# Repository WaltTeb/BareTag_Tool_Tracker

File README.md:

# Baretag Tool-Tracker

Item locating and theft prevention system built around the DWM3001C using Ultra Wideband, BLE, and LoRa technologies.

## Hardware

Qorvo DWM3001C - UWB & BLE SoC using nRF52833 and Qorvo DWM3000  

Reyax RYLR998 - LoRa  

3.7V 290mAh LiPo - Tag Battery  

3.7 2200mAh LiIon - Anchor Battery  

CP2102 Serial Converter - LoRa to Serial  

Raspberry Pi 4B - Host for Lora processing  

Dell NUC - Host for servers  

Tag-Connect Edge-Connect Programmer - Programming Tag PCBs  

SEGGER JLink Edu Mini - Programming Anchor PCBs  

## Software

SEGGER Embedded Studio - Build environement  

nRF5 SDK - Nordic libraries for nRF52833  

Xcode - UI/UX  

Debian Linux - Light distro for NUC  

J-Flash Lite - Flashing firmware to DWM3001C  

SQLite - Database management  

Electron - App development  

KiCad - PCB design   
 
# Setup

Run the shell script that we have yet to make in order to install project dependencies
This will create a working project development environment

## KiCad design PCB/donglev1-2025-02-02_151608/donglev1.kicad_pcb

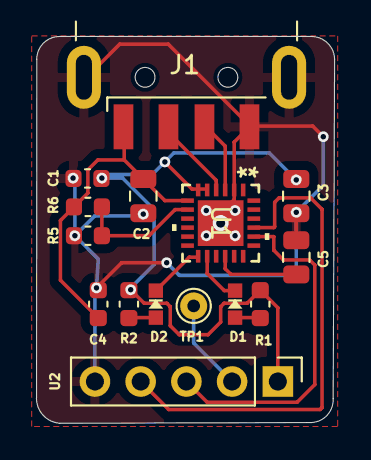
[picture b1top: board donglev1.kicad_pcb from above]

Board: 2 copper layers, 16.6 x 21.5 mm, 15 parts (0 on the bottom side), 12 nets.

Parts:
C1, C4: C0603C104J4RACTU; C_0603_1608Metric
C2, C3, C5: C0603C106M9PAC7867; C_0805_2012Metric
D1: D1; CHIPLED_0603_NOOUTLINE
D2: D2; CHIPLED_0603_NOOUTLINE
J1: 1734028-1; USB_A_CNCTech_1001-011-01101_Horizontal
R1, R2, R6: RT0603BRD0720KL; C_0603_1608Metric
R5: RC0603FR-0747KL; C_0603_1608Metric
TP1: TestPoint; TestPoint_THTPad_D1.5mm_Drill0.7mm
U1: CP2102N-24; QFN24_CP2102N_SIL-L
U2: RYLR998; PinHeader_1x05_P2.54mm_Vertical

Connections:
+3.3V: C1.1, C3.1, R1.2, R2.2, U1.5 (VIO), U1.6 (VDD), U2.1
+5V: C2.1, C4.1, J1.1 (VBUS), R6.2, U1.7 (REGIN)
/D+: J1.3 (D+), U1.3 (D+)
/D-: J1.2 (D-), U1.4 (D-)
/RSTL: TP1.1, U2.2
/RX: U1.20 (RXD), U2.3
/TX: U1.21 (TXD), U2.4
/VBUS_DETECT: R5.2, R6.1, U1.8 (VBUS)
GND: C1.2, C2.2, C3.2, C4.2, C5.2, J1.4 (GND), J1.5 (Shield), R5.1, U1.2 (GND), U2.5
unnamed: C5.1, U1.16 (CP2014VREG)
unnamed: D1.C, U1.14 (GPIO0/TXLED)
unnamed: D2.C, U1.13 (GPIO1/RXLED)

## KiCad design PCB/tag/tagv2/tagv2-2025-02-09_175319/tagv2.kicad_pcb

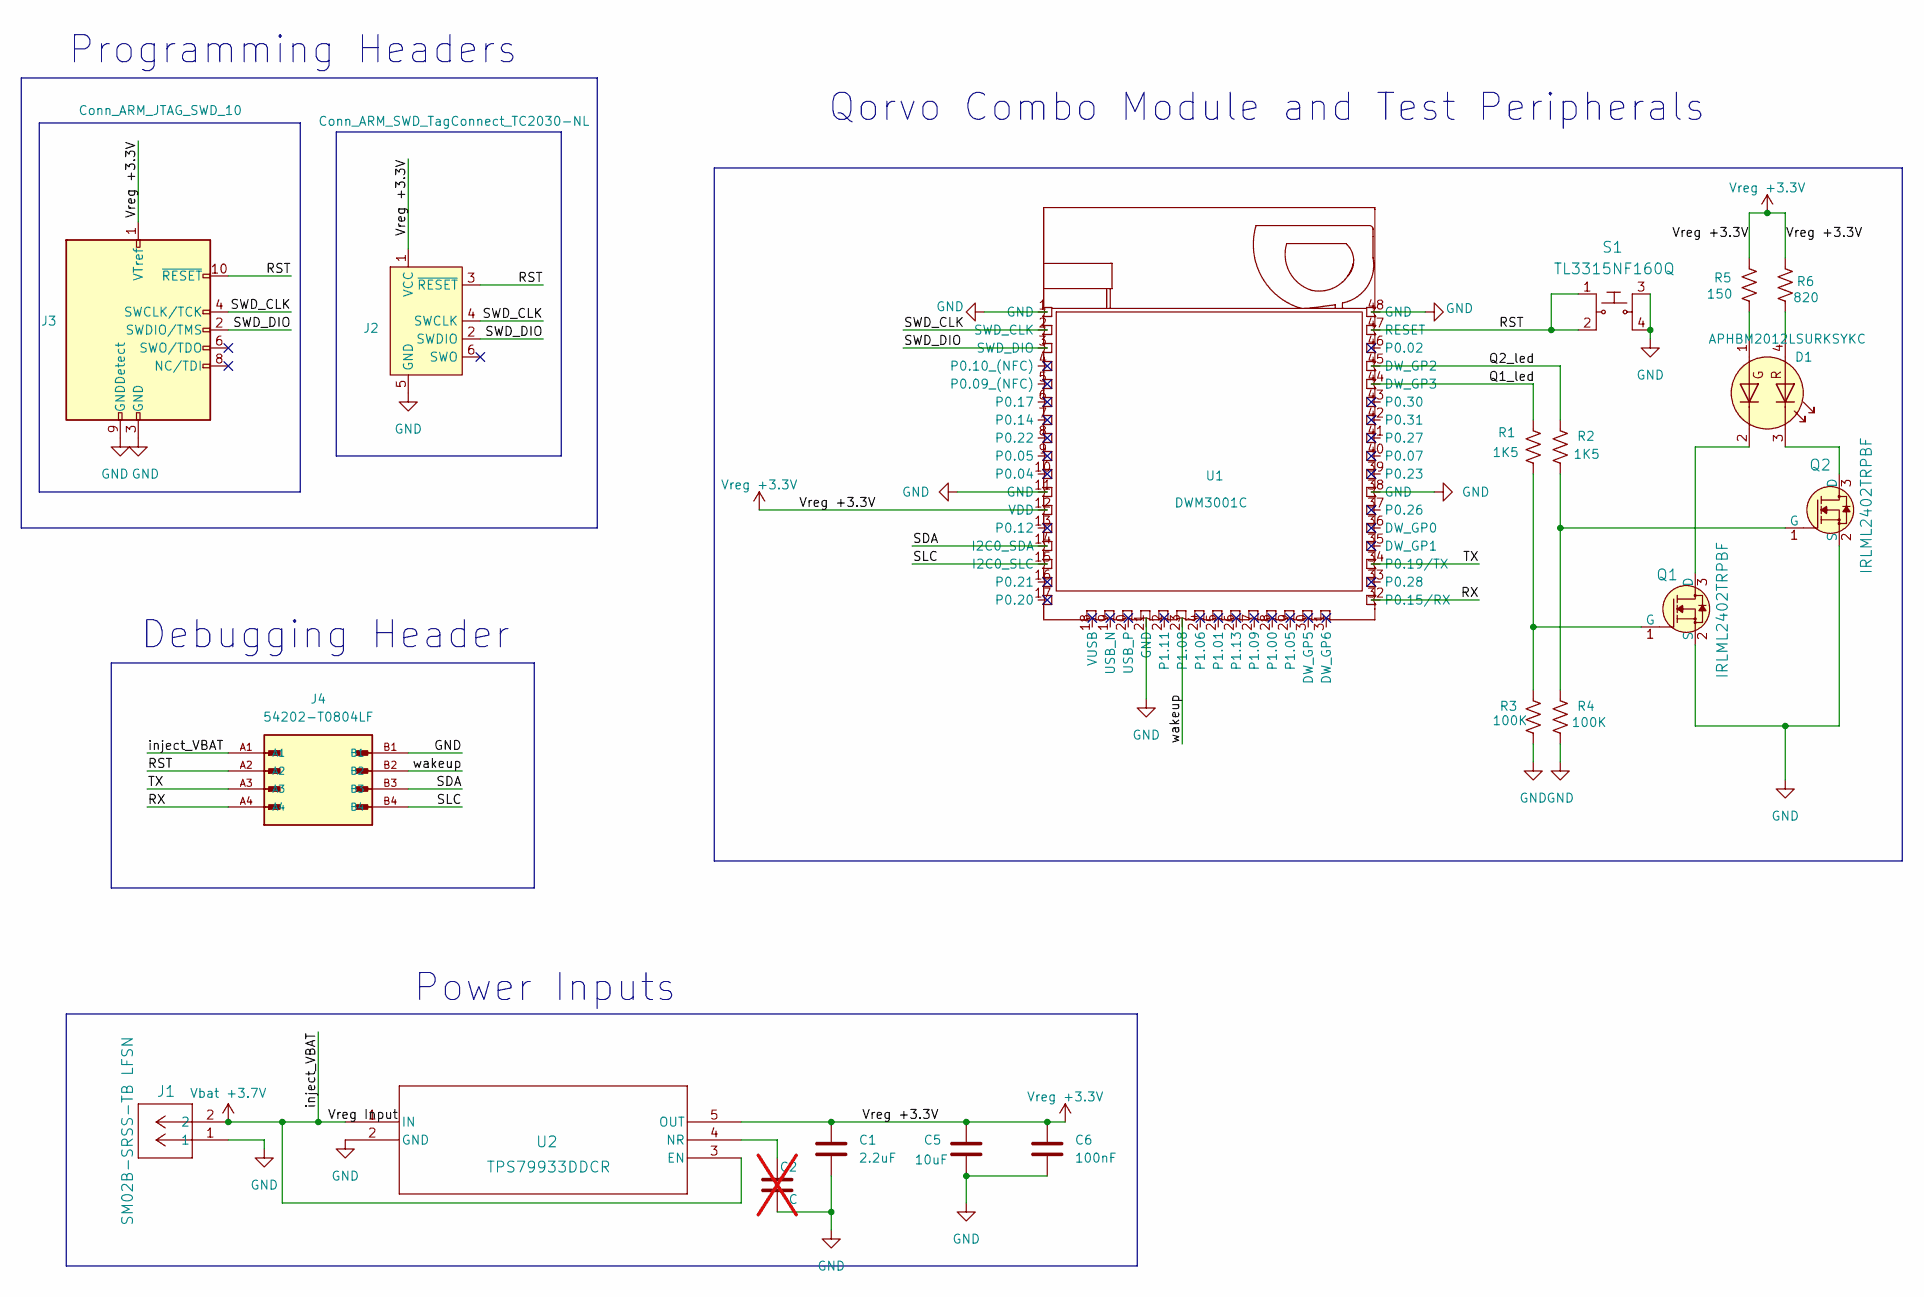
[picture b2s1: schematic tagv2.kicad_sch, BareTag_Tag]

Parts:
C1: 2.2uF; GRM155C80J225KE95D
C2: C; GRM155C80J225KE95D; not fitted
C5: 10uF; GRM155C80J225KE95D
C6: 100nF; C_0603_1608Metric
D1: APHBM2012LSURKSYKC; LED_APHBM2012LSURKSYKC
J1: SM02B-SRSS-TB LFSN; SM02BSRSSTBLFSN
J2: Conn_ARM_SWD_TagConnect_TC2030-NL
J3: Conn_ARM_JTAG_SWD_10; PinHeader_2x05_P1.27mm_Vertical_SMD
J4: 54202-T0804LF; AMPHENOL_54202-T0804LF; PARTREV AC
Q1, Q2: IRLML2402TRPBF; SOT-23-3; MPN IRLML2402TRPBF; Digi-Key_PN IRLML2402PBFCT-ND
R1, R2: 1K5; R_0402_1005Metric
R3, R4: 100K; R_0402_1005Metric
R5: 150; R_0402_1005Metric
R6: 820; R_0402_1005Metric
S1: TL3315NF160Q; Switch_Tactile_SMD_4.5x4.5mm_TL3315NF160Q; MPN TL3315NF160Q; Digi-Key_PN EG4621CT-ND
U1: DWM3001C
U2: TPS79933DDCR; SOT95P280X110-5N

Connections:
/Q1_led: R1.1, U1.44 (DW_GP3)
/Q2_led: R2.1, U1.45 (DW_GP2)
/RST: J2.3 (~RESET), J3.10 (~RESET), J4.A2, S1.1, S1.2, U1.47 (RESET); also elsewhere on the board
/RX: J4.A4, U1.32 (P0.15/RX); also elsewhere on the board
/SDA: J4.B3, U1.14 (I2C0_SDA); also elsewhere on the board
/SLC: J4.B4, U1.15 (I2C0_SLC); also elsewhere on the board
/SWD_CLK: J2.4 (SWCLK), J3.4 (SWCLK/TCK), U1.2 (SWD_CLK)
/SWD_DIO: J2.2 (SWDIO), J3.2 (SWDIO/TMS), U1.3 (SWD_DIO)
/TX: J4.A3, U1.34 (P0.19/TX); also elsewhere on the board
/wakeup: J4.B2, U1.23 (P1.08); also elsewhere on the board
GND: C1.1, C2.2, C5.2, C6.2, J1.1, J2.5 (GND), J3.3 (GND), J3.5 (GND), J3.9 (GNDDetect), Q1.2 (S), Q2.2 (S), R3.2, R4.2, S1.3, S1.4, U1.1 (GND), U1.11 (GND), U1.21 (GND), U1.38 (GND), U1.48 (GND), U2.2 (GND); also elsewhere on the board
unnamed: D1.4 (A1), R6.2
unnamed: D1.1 (A2), R5.2
unnamed: D1.3 (K1), Q2.3 (D)
unnamed: D1.2 (K2), Q1.3 (D)
unnamed: Q1.1 (G), R1.2, R3.1
unnamed: Q2.1 (G), R2.2, R4.1
unnamed: C2.1, U2.4 (NR)
Vbat +3.7V: J1.2, J4.A1, U2.1 (IN), U2.3 (EN); also elsewhere on the board
Vreg +3.3V: C1.2, C5.1, C6.1, J2.1 (VCC), J3.1 (VTref), R5.1, R6.1, U1.12 (VDD), U2.5 (OUT)

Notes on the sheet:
Qorvo Combo Module and Test Peripherals
Debugging Header
Power Inputs
Programming Headers

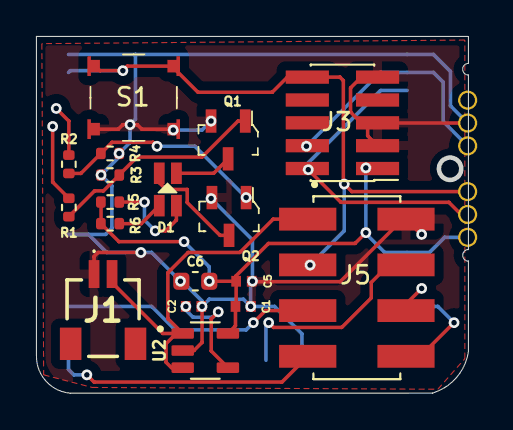
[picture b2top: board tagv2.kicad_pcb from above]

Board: 2 copper layers, 23.8 x 19.6 mm, 19 parts (1 on the bottom side), 20 nets.

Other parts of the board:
J5: 54202-T0804LF; AMPHENOL_54202-T0804LF

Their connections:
/RST: J5.A2; also elsewhere on the board
/RX: J5.A4; also elsewhere on the board
/SDA: J5.B3; also elsewhere on the board
/SLC: J5.B4; also elsewhere on the board
/TX: J5.A3; also elsewhere on the board
/wakeup: J5.B2; also elsewhere on the board
GND: J5.B1; also elsewhere on the board
Vbat +3.7V: J5.A1; also elsewhere on the board

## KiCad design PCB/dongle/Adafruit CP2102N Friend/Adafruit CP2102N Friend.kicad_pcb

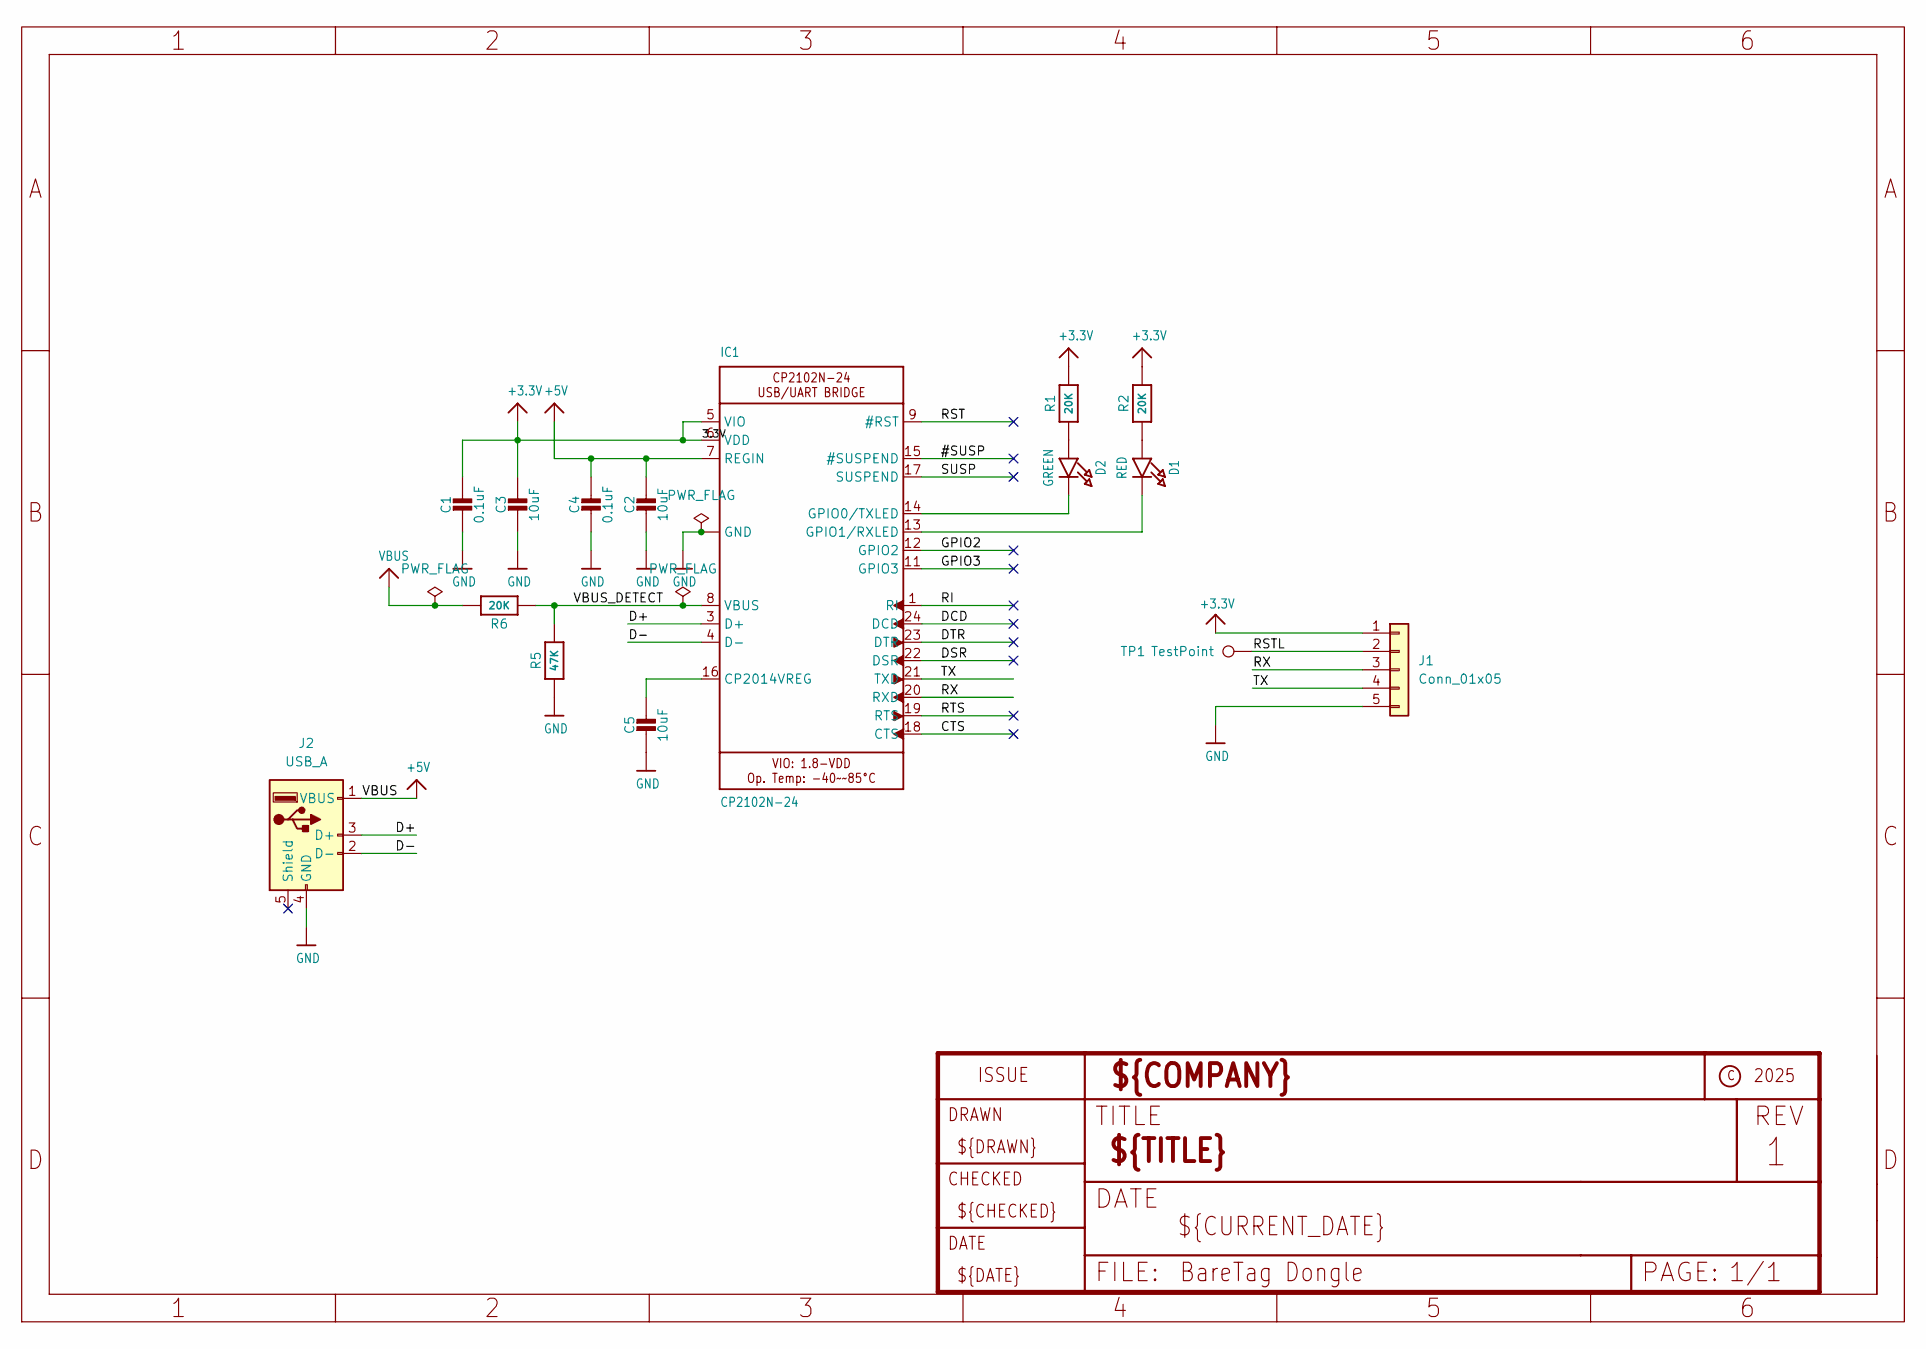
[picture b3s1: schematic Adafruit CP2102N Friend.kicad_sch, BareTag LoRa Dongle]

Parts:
C1, C4: 0.1uF; C_0603_1608Metric
C2, C3, C5: 10uF; C_0805_2012Metric
D1: RED; CHIPLED_0603_NOOUTLINE
D2: GREEN; CHIPLED_0603_NOOUTLINE
IC1: CP2102N-24; QFN24_CP2102N_SIL
J1: Conn_01x05; PinHeader_1x05_P2.54mm_Vertical
J2: USB_A; 17340281
R1, R2, R6: 20K; C_0603_1608Metric
R5: 47K; C_0603_1608Metric
TP1: TestPoint; TestPoint_THTPad_D1.5mm_Drill0.7mm

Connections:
+3.3V: C1.1, C3.1, IC1.5 (VIO), IC1.6 (VDD), J1.1, R1.2, R2.2
+5V: C2.1, C4.1, IC1.7 (REGIN), J2.1 (VBUS), R6.2
/#SUSP: IC1.15 (#SUSPEND)
/CTS: IC1.18 (CTS)
/D+: IC1.3 (D+), J2.3 (D+)
/D-: IC1.4 (D-), J2.2 (D-)
/DCD: IC1.24 (DCD)
/DSR: IC1.22 (DSR)
/DTR: IC1.23 (DTR)
/GPIO2: IC1.12 (GPIO2)
/GPIO3: IC1.11 (GPIO3)
/RI: IC1.1 (RI)
/RST: IC1.9 (#RST)
/RSTL: J1.2, TP1.1
/RTS: IC1.19 (RTS)
/RX: IC1.20 (RXD), J1.3
/SUSP: IC1.17 (SUSPEND)
/TX: IC1.21 (TXD), J1.4
/VBUS_DETECT: IC1.8 (VBUS), R5.2, R6.1
GND: C1.2, C2.2, C3.2, C4.2, C5.2, IC1.2 (GND), IC1.THERM (GND), J1.5, J2.4 (GND), R5.1
unnamed: D1.A, R2.1
unnamed: D2.A, R1.1
unnamed: C5.1, IC1.16 (CP2014VREG)
unnamed: D2.C, IC1.14 (GPIO0/TXLED)
unnamed: D1.C, IC1.13 (GPIO1/RXLED)

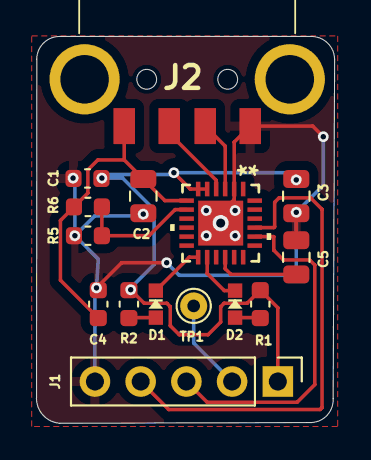
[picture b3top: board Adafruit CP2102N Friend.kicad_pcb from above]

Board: 2 copper layers, 16.6 x 21.5 mm, 15 parts (0 on the bottom side), 14 nets.

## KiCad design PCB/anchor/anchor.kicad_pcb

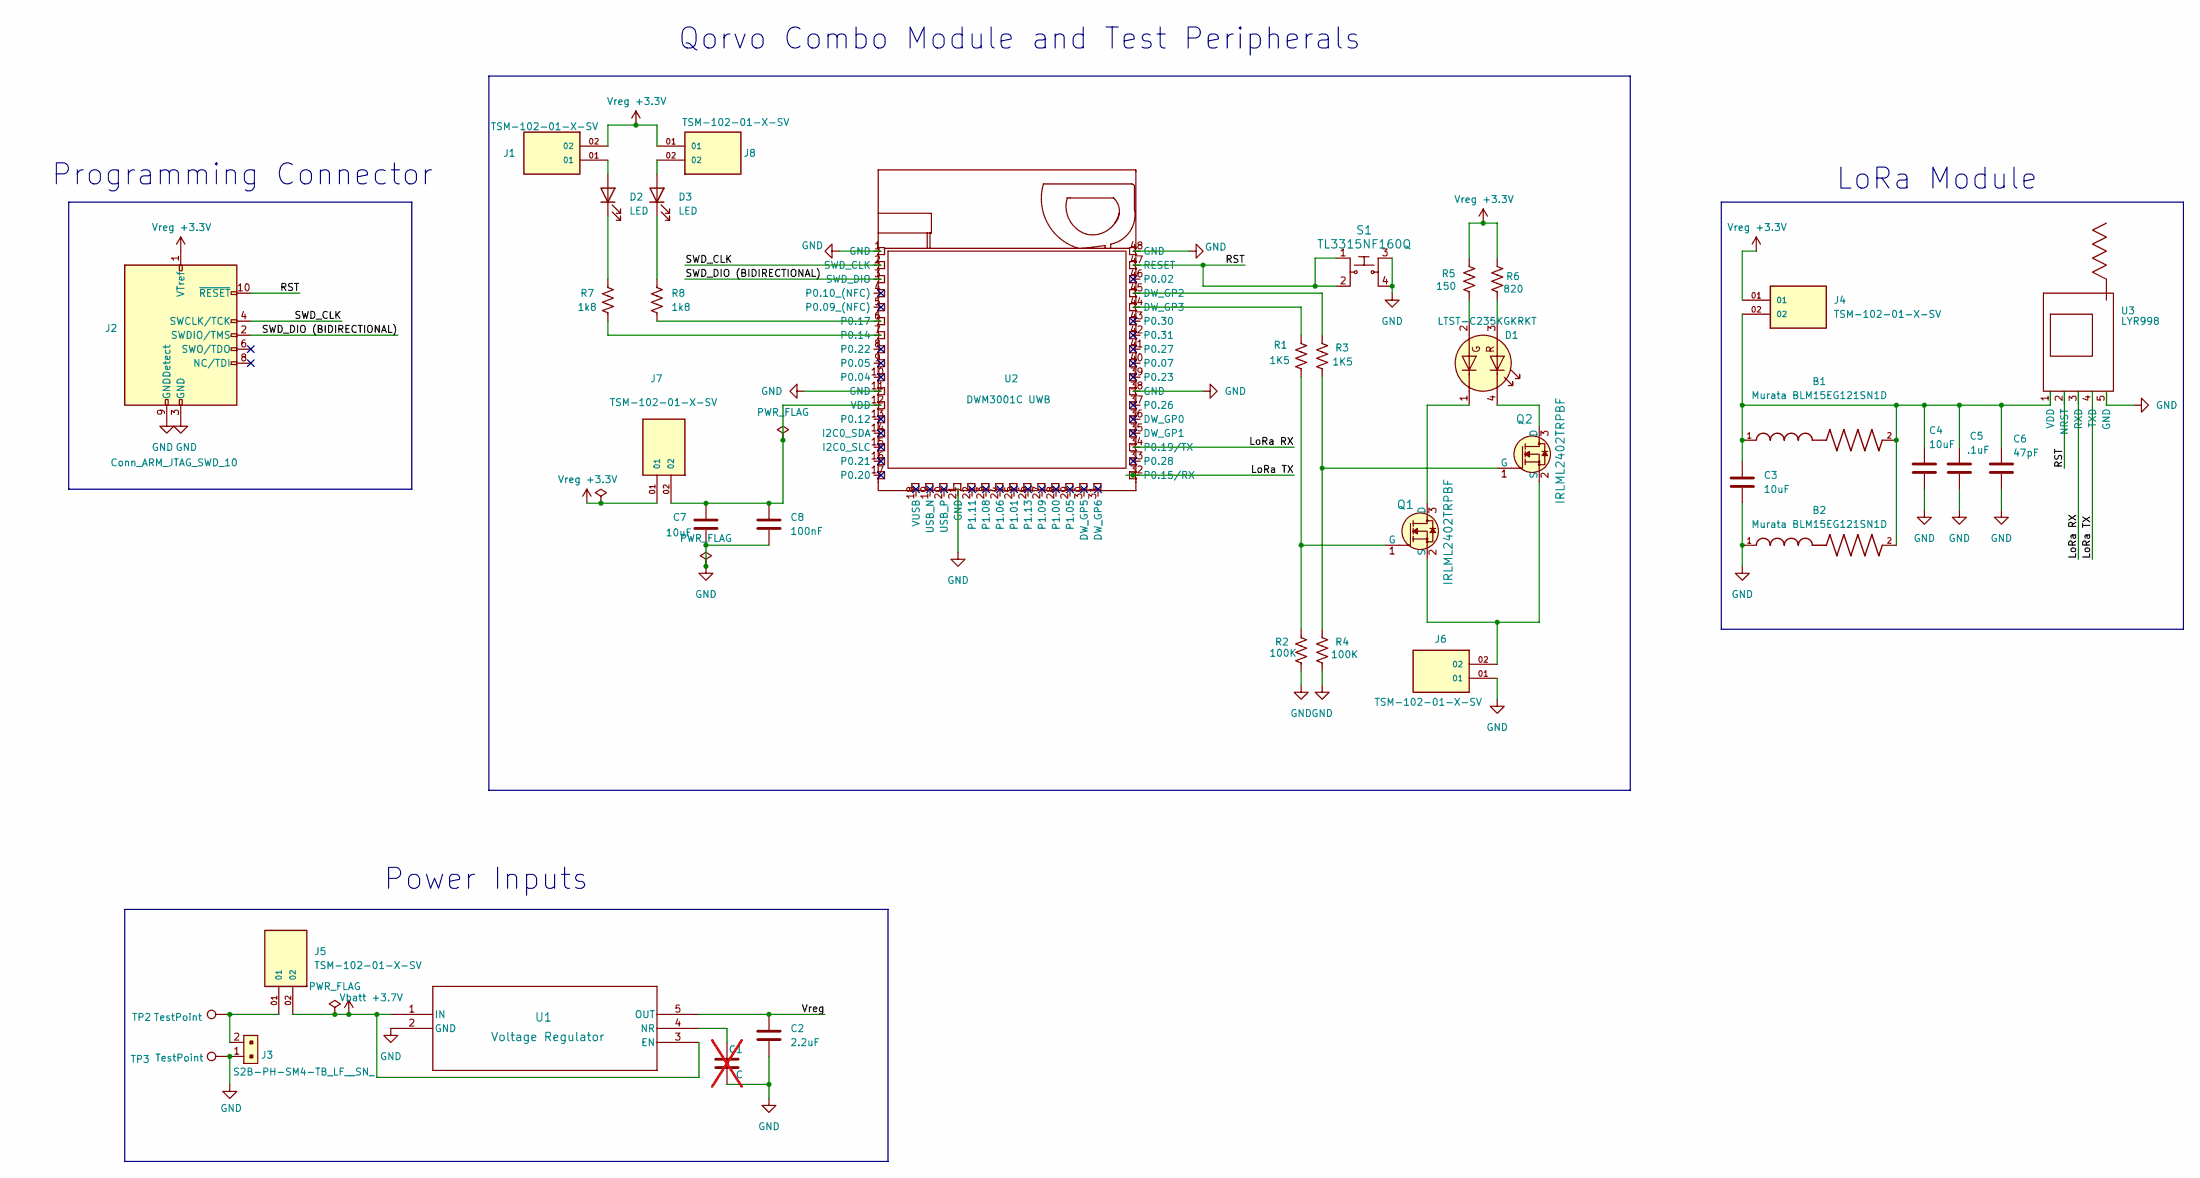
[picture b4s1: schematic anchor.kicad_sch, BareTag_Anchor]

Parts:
B1, B2: Murata BLM15EG121SN1D; BEADC1005X55N; DigiKey_Part_Number 490-4004-2-ND
C1: C; GRM155C80J225KE95D; not fitted
C2: 2.2uF; CAPC1005X55N
C3, C4, C7: 10uF; CAPC1005X70N
C5: .1uF; CAPC1005X55N
C6: 47pF; CAPC1005X55N
C8: 100nF
D1: LTST-C235KGKRKT; LED_LiteOn_LTST-C235KGKRKT
D2, D3: LED
J1, J4, J5, J6, J7, J8: TSM-102-01-X-SV; SAMTEC_TSM-102-01-X-SV; PARTREV D
J2: Conn_ARM_JTAG_SWD_10; PinHeader_2x05_P1.27mm_Vertical_SMD
J3: S2B-PH-SM4-TB_LF__SN_; PinHeader_2x1mm_P2mm_SMD_RA; MPN S2B-PH-SM4-TB(LF)(SN); Digi-Key_PN 455-1749-1-ND
Q1, Q2: IRLML2402TRPBF; SOT-23-3; MPN IRLML2402TRPBF; Digi-Key_PN IRLML2402PBFCT-ND
R1, R3: 1K5
R2, R4: 100K
R5: 150
R6: 820
R7, R8: 1k8
S1: TL3315NF160Q; Switch_Tactile_SMD_4.5x4.5mm_TL3315NF160Q; MPN TL3315NF160Q; Digi-Key_PN EG4621CT-ND
TP2, TP3: TestPoint
U1: Voltage Regulator; DDC5
U2: DWM3001C UWB; DWM3001C
U3: LYR998; PinHeader_1x05_P2.54mm_Vertical

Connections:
/LoRa RX: U2.34 (P0.19/TX), U3.3 (RXD)
/LoRa TX: U2.32 (P0.15/RX), U3.4 (TXD)
/RST: J2.10 (~RESET), S1.1, S1.2, U2.47 (RESET), U3.2 (NRST)
/SWD_CLK: J2.4 (SWCLK/TCK), U2.2 (SWD_CLK)
/SWD_DIO (BIDIRECTIONAL): J2.2 (SWDIO/TMS), U2.3 (SWD_DIO)
GND: B2.1, C1.2, C2.1, C3.2, C4.2, C5.2, C6.2, C7.2, C8.2, J2.3 (GND), J2.5 (GND), J2.9 (GNDDetect), J3.1, J6.01, R2.2, R4.2, S1.3, S1.4, TP3.1, U1.2 (GND), U2.1 (GND), U2.11 (GND), U2.21 (GND), U2.38 (GND), U2.48 (GND), U3.5 (GND)
unnamed: D1.3 (A1), R6.2
unnamed: D1.2 (A2), R5.2
unnamed: D1.4 (K1), Q2.3 (D)
unnamed: D1.1 (K2), Q1.3 (D)
unnamed: D2.2 (A), J1.01
unnamed: D2.1 (K), R7.1
unnamed: D3.2 (A), J8.02
unnamed: D3.1 (K), R8.1
unnamed: J3.2, J5.01, TP2.1
unnamed: Q1.1 (G), R1.2, R2.1
unnamed: J6.02, Q1.2 (S), Q2.2 (S)
unnamed: Q2.1 (G), R3.2, R4.1
unnamed: C1.1, U1.4 (NR)
unnamed: R3.1, U2.45 (DW_GP2)
unnamed: R1.1, U2.44 (DW_GP3)
unnamed: R7.2, U2.7 (P0.14)
unnamed: R8.2, U2.6 (P0.17)
unnamed: C7.1, C8.1, J7.02, U2.12 (VDD)
unnamed: B1.1, B1.2, B2.2, C3.1, C4.1, C5.1, C6.1, J4.02, U3.1 (VDD)
Vbatt +3.7V: J5.02, U1.1 (IN), U1.3 (EN)

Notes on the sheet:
LoRa Module
Power Inputs
Qorvo Combo Module and Test Peripherals
Programming Connector

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
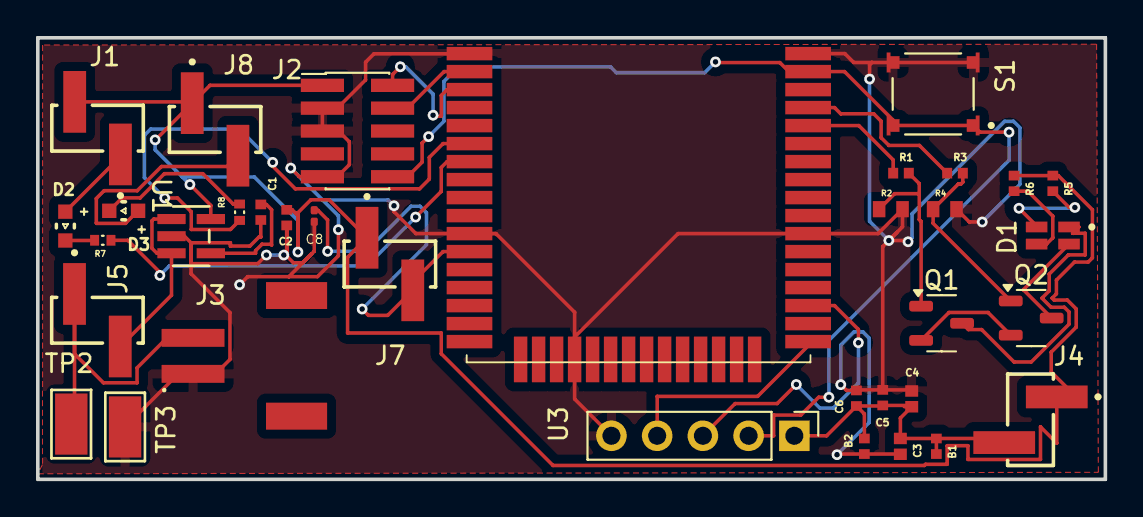
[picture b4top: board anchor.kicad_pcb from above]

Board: 2 copper layers, 59.3 x 24.5 mm, 35 parts (0 on the bottom side), 27 nets.

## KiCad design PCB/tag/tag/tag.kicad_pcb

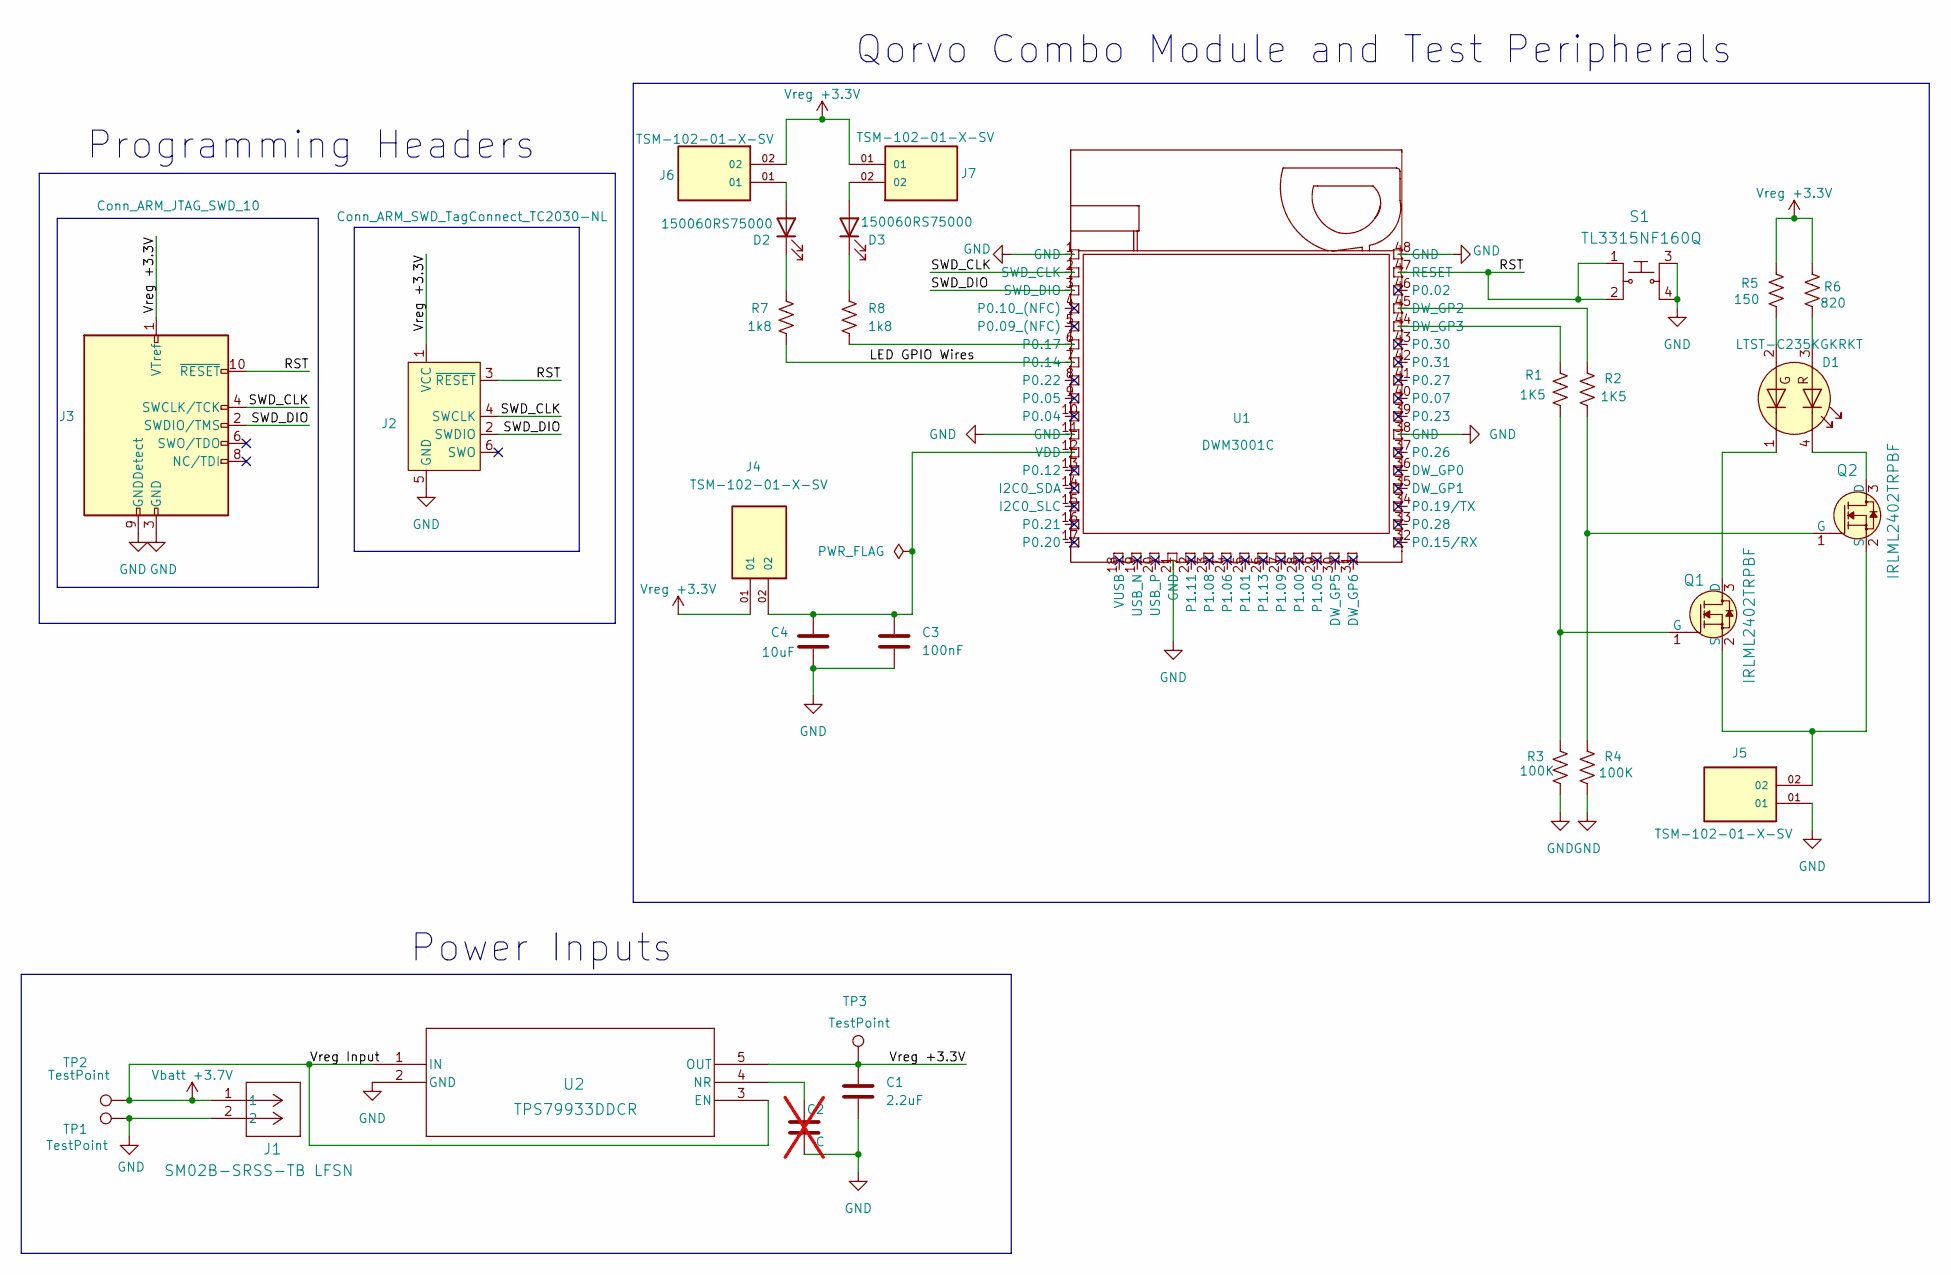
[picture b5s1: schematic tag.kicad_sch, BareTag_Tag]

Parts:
C1: 2.2uF; GRM155C80J225KE95D
C2: C; GRM155C80J225KE95D; not fitted
C3: 100nF
C4: 10uF
D1: LTST-C235KGKRKT; LED_LiteOn_LTST-C235KGKRKT
D2, D3: 150060RS75000
J1: SM02B-SRSS-TB LFSN; CONN_SM02B-SRSS-TB_JST
J2: Conn_ARM_SWD_TagConnect_TC2030-NL; Tag-Connect_TC2030-IDC-NL_2x03_P1.27mm_Vertical
J3: Conn_ARM_JTAG_SWD_10; PinHeader_2x05_P1.27mm_Vertical_SMD
J4, J5, J6, J7: TSM-102-01-X-SV; SAMTEC_TSM-102-01-X-SV; PARTREV D
Q1, Q2: IRLML2402TRPBF; SOT-23-3; MPN IRLML2402TRPBF; Digi-Key_PN IRLML2402PBFCT-ND
R1, R2: 1K5
R3, R4: 100K
R5: 150
R6: 820
R7, R8: 1k8
S1: TL3315NF160Q; Switch_Tactile_SMD_4.5x4.5mm_TL3315NF160Q; MPN TL3315NF160Q; Digi-Key_PN EG4621CT-ND
TP1, TP2, TP3: TestPoint
U1: DWM3001C
U2: TPS79933DDCR; DDC5

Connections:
/3001vdd: C3.1, C4.1, J4.02, U1.12 (VDD)
/RST: J2.3 (~RESET), J3.10 (~RESET), S1.1, S1.2, U1.47 (RESET)
/SWD_CLK: J2.4 (SWCLK), J3.4 (SWCLK/TCK), U1.2 (SWD_CLK)
/SWD_DIO: J2.2 (SWDIO), J3.2 (SWDIO/TMS), U1.3 (SWD_DIO)
GND: C1.1, C2.2, C3.2, C4.2, J1.2, J2.5 (GND), J3.3 (GND), J3.5 (GND), J3.9 (GNDDetect), J5.01, R3.2, R4.2, S1.3, S1.4, TP1.1, U1.1 (GND), U1.11 (GND), U1.21 (GND), U1.38 (GND), U1.48 (GND), U2.2 (GND)
unnamed: D1.3 (A1), R6.2
unnamed: D1.2 (A2), R5.2
unnamed: D1.4 (K1), Q2.3 (D)
unnamed: D1.1 (K2), Q1.3 (D)
unnamed: D2.2 (A), J6.01
unnamed: D2.1 (K), R7.1
unnamed: D3.2 (A), J7.02
unnamed: D3.1 (K), R8.1
unnamed: Q1.1 (G), R1.2, R3.1
unnamed: J5.02, Q1.2 (S), Q2.2 (S)
unnamed: Q2.1 (G), R2.2, R4.1
unnamed: R2.1, U1.45 (DW_GP2)
unnamed: R1.1, U1.44 (DW_GP3)
unnamed: R7.2, U1.7 (P0.14)
unnamed: R8.2, U1.6 (P0.17)
unnamed: C2.1, U2.4 (NR)
Vbatt +3.7V: J1.1, TP2.1, U2.1 (IN), U2.3 (EN)
Vreg +3.3V: C1.2, J2.1 (VCC), J3.1 (VTref), J4.01, J6.02, J7.01, R5.1, R6.1, TP3.1, U2.5 (OUT)

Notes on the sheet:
Qorvo Combo Module and Test Peripherals
Power Inputs
Programming Headers

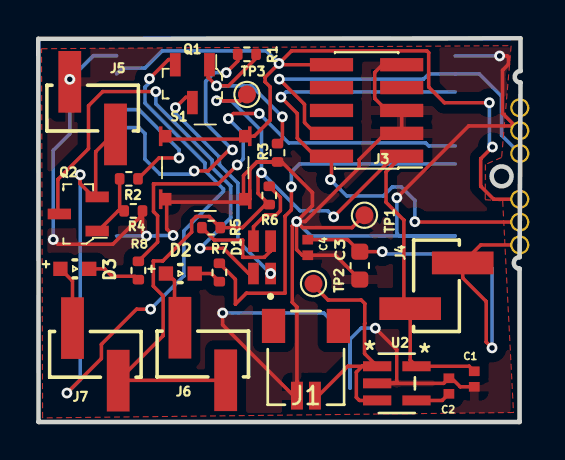
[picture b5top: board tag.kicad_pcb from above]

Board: 2 copper layers, 26.8 x 21.3 mm, 29 parts (1 on the bottom side), 23 nets.

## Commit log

2024-10-14 added Tex file
2024-10-15 wrote abstract
2024-10-18 ieee template + significance
2024-10-18 uploaded ieee template in words format
2024-10-18 blah
2024-10-19 {Added my latest changes into latex, did some name formatting, and added the hardware block diagram}
2024-10-19 clarified subsections
2024-10-20 finished design overview, and reformatted
2024-10-21 reformatted, ready for final proof read
2024-10-21 proof read ken's writing
2024-10-21 deleted pdf
2024-10-21 changed anchor to Anchor
2024-10-22 Changed repo to full project repo
2024-10-23 Add PCB folder. This includes the KiKad folders and some of the custom content that I have made
2024-10-24 updated anchor pcb + DWM Datasheet
2024-10-24 pcb stuff
2024-10-24 updated Tag PCB
2024-10-25 Tag and Anchor schematic updates
2024-10-25 touch
2024-10-25 maybe updates?
2024-10-25 PCB updates
2024-10-25 added .gitignore to the PCB directory
2024-10-29 this is the newest folder status
2024-10-29 delete
2024-10-29 final
2024-10-29 added footprint folder and footprints to the cap's
2024-10-31 updated pcb for anchor
2024-11-01 final tag
2024-11-01 anchor PCB v1
2024-11-01 pdf file of anchor pics
2024-11-17 added dwm3001c starter firmware to the repo
2024-11-17 added openhaystack related materials and important firmwares. Will be changing readmes and organizing stuff fr later
2024-11-17 consolidated
2024-11-25 got trilateration working
2024-11-25 testing trilateration
2024-12-19 mdr report update
2025-01-30 new pcb
2025-02-01 readme test
2025-02-01 moved project build off of Docker, and simplified files
2025-02-01 idk, connor did PCB stuff
2025-02-01 modified gitignore
2025-02-01 deleted build
2025-02-01 modifying gitignore
2025-02-01 testing a merge
2025-02-01 kicad readme
2025-02-01 conflict test
2025-02-02 PCB folder organization
2025-02-02 got UART RX working
2025-02-02 ignoring Output/
2025-02-02 added comments
2025-02-04 toggle led on interrupt
2025-02-04 tweaks
2025-02-04 Makefile changes to locate SES if it's in in /usr/*
2025-02-04 added SES session file to the gitignore
2025-02-04 include fixes and gitignore updates
2025-02-05 testing responder
2025-02-05 fixed connor's mistakes
2025-02-08 timer tests
2025-02-09 dongle??
2025-02-10 fingle
2025-02-10 actual working pcb backups
2025-02-22 other firmware testing
2025-02-22 alternatice testing
